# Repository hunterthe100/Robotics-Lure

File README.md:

# Robotics-Lure (Not named yet)
A lure for the MinnowBoard Max & MinnowBoard Turbot.  Copyright (C) 2015 Smallworks, LLC

This design is made with [EAGLE CAD](http://www.cadsoftusa.com/eagle-pcb-design-software/about-eagle/) 

This work is licensed under a Creative Commons Attribution-ShareAlike 4.0 International License
[  
*Licensing CC BY-SA 4.0*](http://creativecommons.org/licenses/by-sa/4.0/)

It may be used for Educational, Personal, or Commercial Use, provided you keep these notices,
attribution, and share-alike. When you apply these licenses to material you create, 
it meets the Freedom Defined definition of a "Free Cultural Work". 
Free cultural works are the ones that can be most readily used, shared, 
and remixed by others, and go furthest toward creating a commons of freely reusable materials.

-------------------------------------------------------------------------------------------

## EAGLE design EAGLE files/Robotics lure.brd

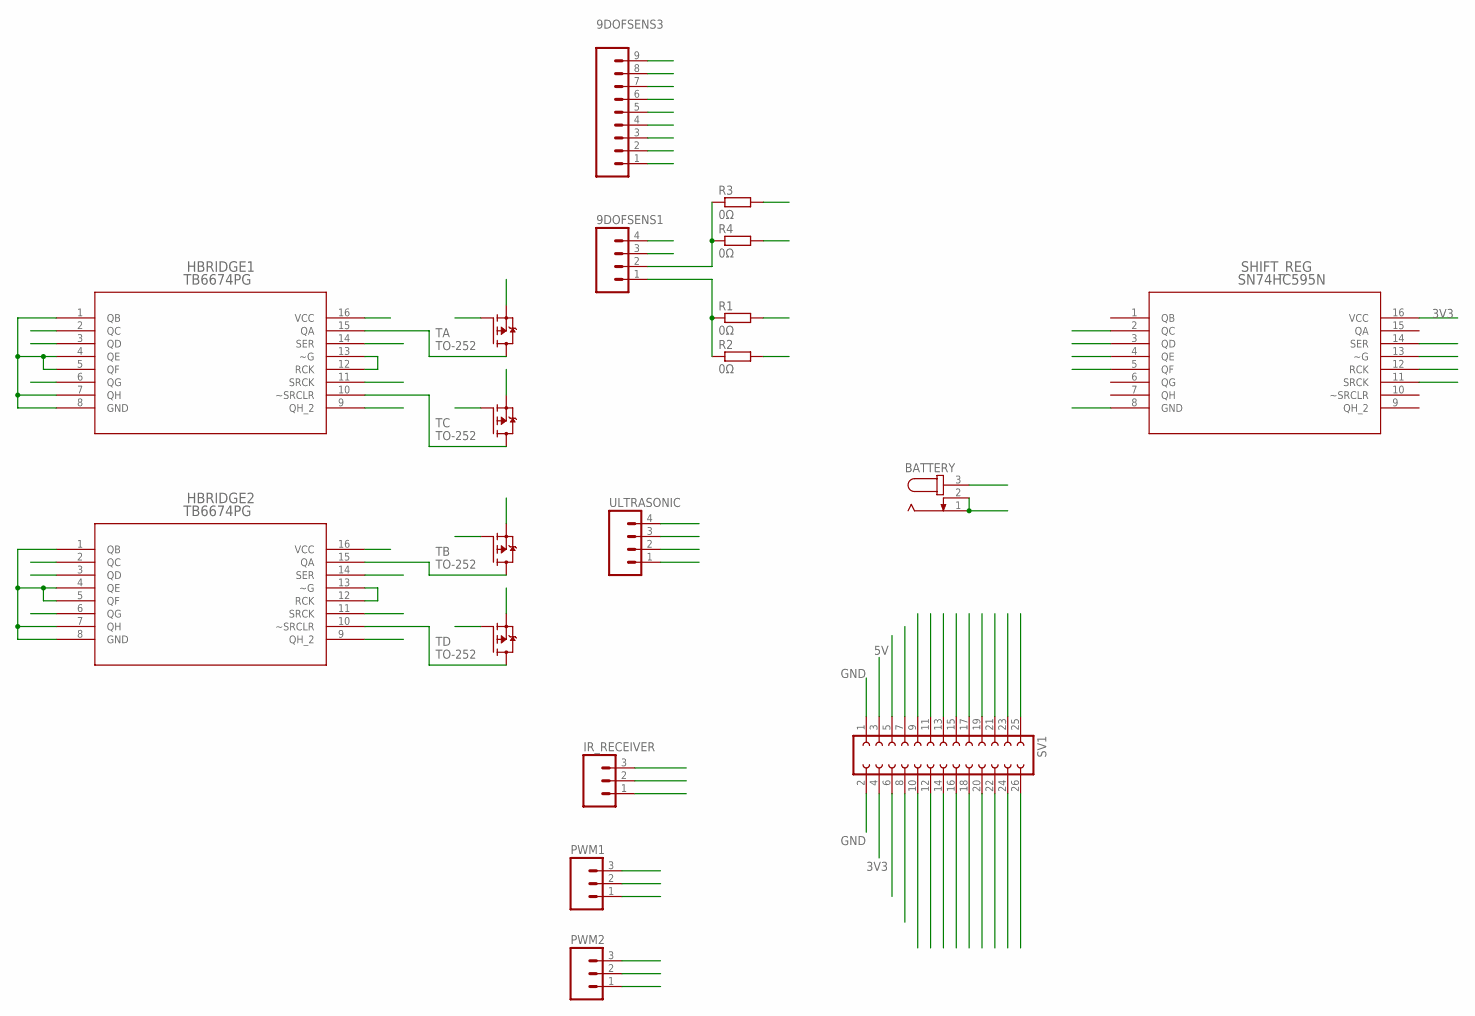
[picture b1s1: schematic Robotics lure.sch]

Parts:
9DOFSENS1: M04PTH; 1X04
9DOFSENS3: M09; 1X09
BATTERY: JACK-PLUG0; SPC4077
HBRIDGE1, HBRIDGE2: TB6674PG; DIP16_300
IR_RECEIVER: M03PTH; 1X03
PWM1, PWM2: M03PTH; 1X03
R1, R2, R3, R4: 0Ω; R1206
SHIFT_REG: SN74HC595N; DIP16_300
SV1: FE13-2W
TA: TO-252; TO252
TB: TO-252; TO252
TC: TO-252; TO252
TD: TO-252; TO252
ULTRASONIC: M04PTH; 1X04

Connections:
3V3: 9DOFSENS1.3, IR_RECEIVER.1, SHIFT_REG.16 (VCC), SV1.4
5V: HBRIDGE1.2 (QC), HBRIDGE2.2 (QC), PWM1.2, PWM2.2, SV1.3, ULTRASONIC.1
14V: BATTERY.3, HBRIDGE1.9 (QH_2), HBRIDGE1.16 (VCC), HBRIDGE2.9 (QH_2), HBRIDGE2.16 (VCC)
GND: 9DOFSENS1.4, BATTERY.1, BATTERY.2, HBRIDGE1.1 (QB), HBRIDGE1.4 (QE), HBRIDGE1.5 (QF), HBRIDGE1.7 (QH), HBRIDGE1.8 (GND), HBRIDGE1.12 (RCK), HBRIDGE1.13 (~G), HBRIDGE2.1 (QB), HBRIDGE2.4 (QE), HBRIDGE2.5 (QF), HBRIDGE2.7 (QH), HBRIDGE2.8 (GND), HBRIDGE2.12 (RCK), HBRIDGE2.13 (~G), IR_RECEIVER.2, PWM1.1, PWM2.1, SHIFT_REG.8 (GND), SV1.1, SV1.2, ULTRASONIC.4
GPIO_I2C_SCL_(I2C#5): R1.2, SV1.13
GPIO_I2C_SDA_(I2C_#5): R3.2, SV1.15
GPIO_I2S_CLK: 9DOFSENS3.1, SV1.14
GPIO_I2S_DI: 9DOFSENS3.3, 9DOFSENS3.8, SV1.20
GPIO_I2S_DO: 9DOFSENS3.5, SV1.18
GPIO_I2S_FRM: SV1.16
GPIO_PWM0: PWM1.3, SV1.22
GPIO_PWM1: PWM2.3, SV1.24
GPIO_S5_0: SHIFT_REG.14 (SER), SV1.21
GPIO_S5_1: SHIFT_REG.13 (~G), SV1.23
GPIO_S5_2: SHIFT_REG.12 (RCK), SV1.25
GPIO_SPI_CLK: R4.2, SV1.11
GPIO_SPI_CS#: SV1.5, ULTRASONIC.2
GPIO_SPI_MISO: 9DOFSENS3.9, SV1.7
GPIO_SPI_MOSI: R2.2, SV1.9
GPIO_UART1_CTS: 9DOFSENS3.7, SV1.10
GPIO_UART1_RTS: 9DOFSENS3.6, SV1.12
GPIO_UART1_RXD: IR_RECEIVER.3, SV1.8
GPIO_UART1_TXD: SV1.6, ULTRASONIC.3
GPIO_UART2_RXD: 9DOFSENS3.2, SV1.19
GPIO_UART2_TXD: 9DOFSENS3.4, SV1.17
I2SMCLK_GPIO: SHIFT_REG.11 (SRCK), SV1.26
MOTA+: TA.2 (S)
MOTA-: HBRIDGE1.14 (SER)
MOTACTRL: HBRIDGE1.3 (QD), SHIFT_REG.2 (QC), TA.1 (G)
MOTB+: TB.2 (S)
MOTB-: HBRIDGE1.11 (SRCK)
MOTBCTRL: HBRIDGE2.3 (QD), SHIFT_REG.3 (QD), TB.1 (G)
MOTC+: TC.2 (S)
MOTC-: HBRIDGE2.14 (SER)
MOTCCTRL: HBRIDGE1.6 (QG), SHIFT_REG.4 (QE), TC.1 (G)
MOTD+: TD.2 (S)
MOTD-: HBRIDGE2.11 (SRCK)
MOTDCTRL: HBRIDGE2.6 (QG), SHIFT_REG.5 (QF), TD.1 (G)
unnamed: HBRIDGE2.15 (QA), TB.3 (D)
unnamed: HBRIDGE2.10 (~SRCLR), TD.3 (D)
unnamed: HBRIDGE1.10 (~SRCLR), TC.3 (D)
unnamed: HBRIDGE1.15 (QA), TA.3 (D)
SCL: 9DOFSENS1.1, R1.1, R2.1
SDA: 9DOFSENS1.2, R3.1, R4.1

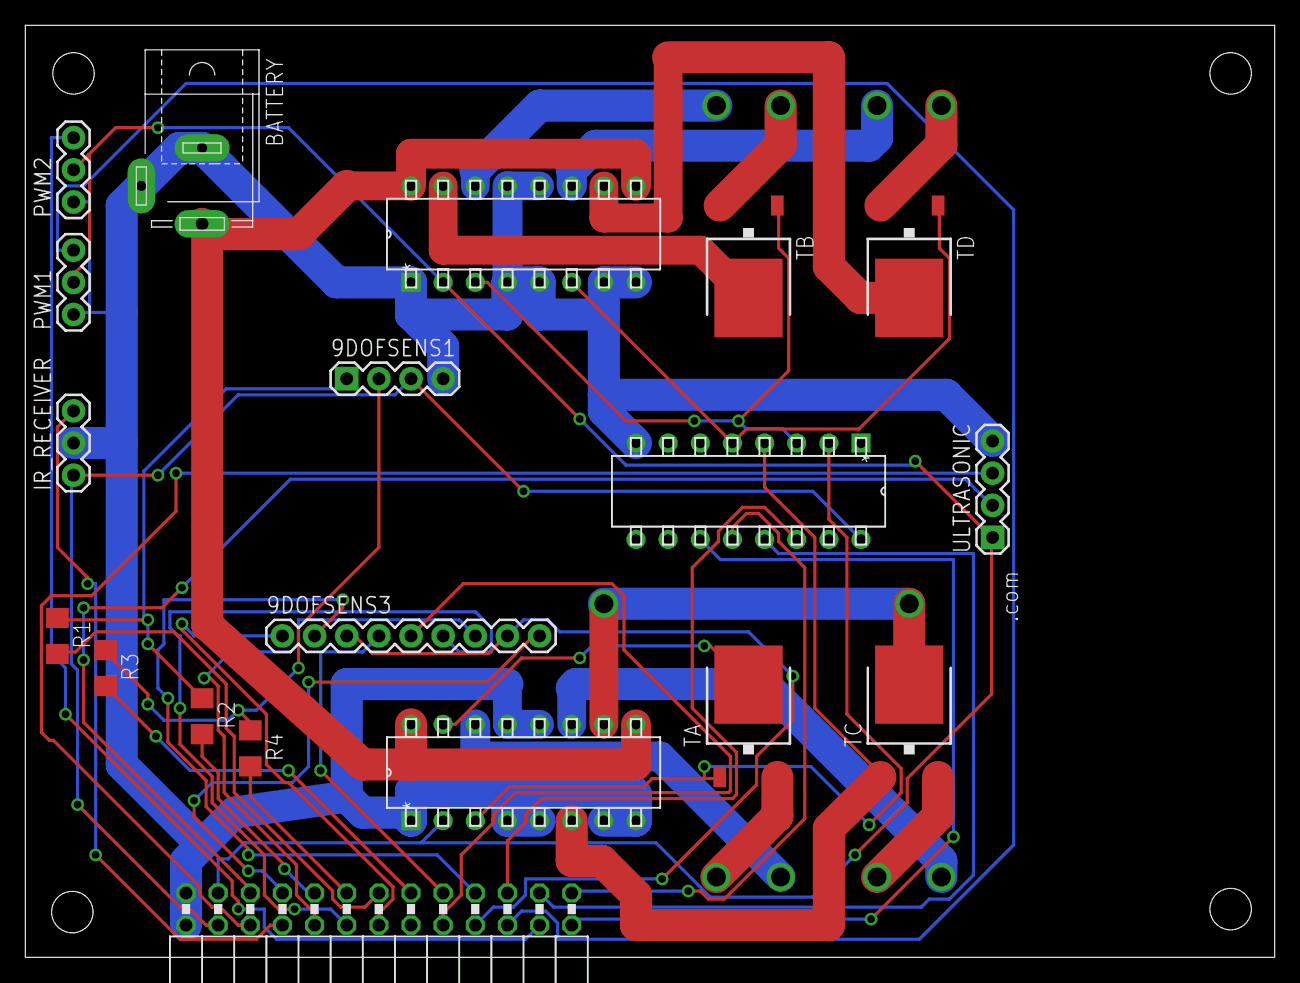
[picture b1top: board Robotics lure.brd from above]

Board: 2 copper layers, 98.7 x 73.7 mm, 19 parts (0 on the bottom side), 35 nets.

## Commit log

2016-07-07 Initial commit
    Robotics lure for the minnow board max & turbo

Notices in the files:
parts and their libraries:
SparkFun-Connectors: Licensing: Creative Commons ShareAlike 4.0 International - https://creativecommons.org/licenses/by-sa/4.0
COPYRIGHT: Copyright (C) 2015 Accelerated Designs. All rights reserved
